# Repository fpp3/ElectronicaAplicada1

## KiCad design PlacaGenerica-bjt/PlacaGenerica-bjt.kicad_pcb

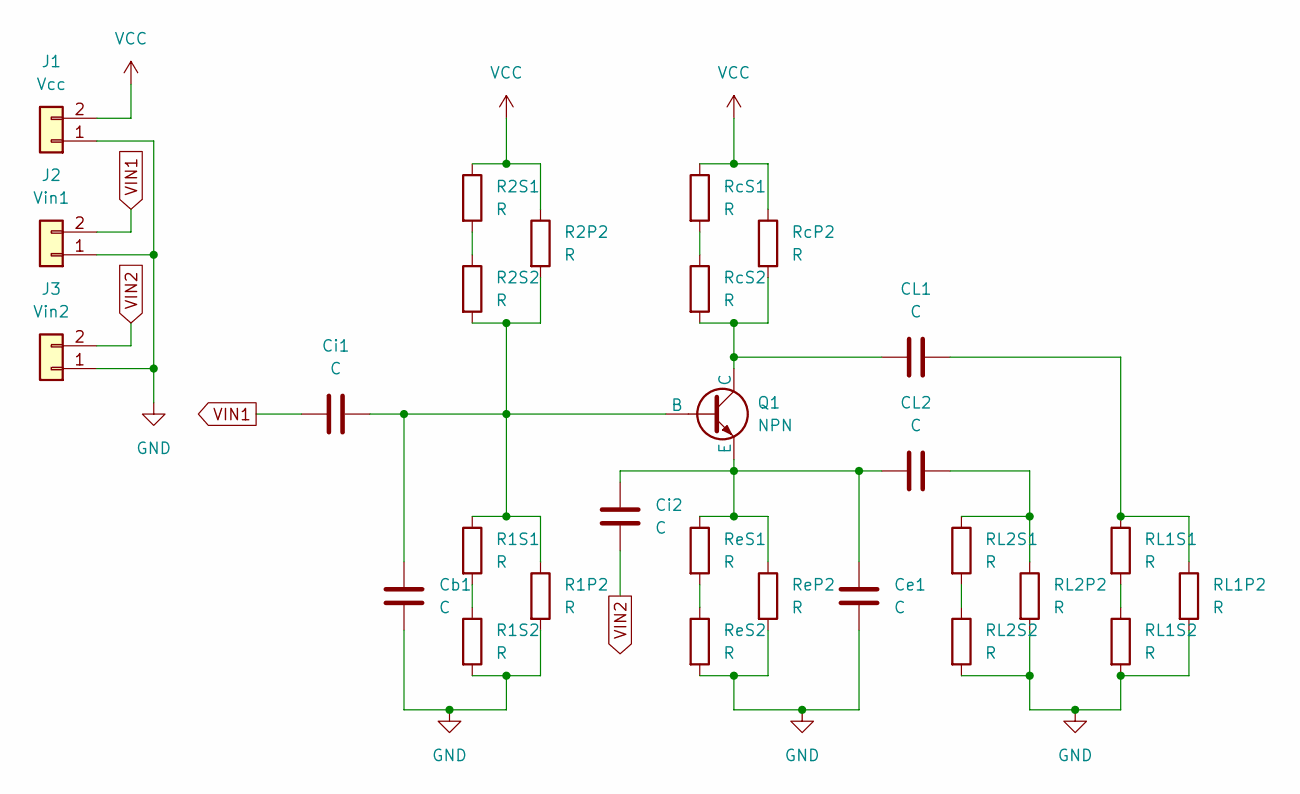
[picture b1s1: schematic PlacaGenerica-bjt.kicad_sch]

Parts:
CL1, CL2: C; Pretty-C_Disc_D5.0mm_W2.5mm_P5.00mm
Cb1: C; Pretty-C_Disc_D5.0mm_W2.5mm_P5.00mm
Ce1: C; Pretty-C_Disc_D5.0mm_W2.5mm_P5.00mm
Ci1, Ci2: C; Pretty-C_Disc_D5.0mm_W2.5mm_P5.00mm
J1: Vcc; TestPoint_2Pads_Pitch5.08mm_Drill1.3mm
J2: Vin1; TestPoint_2Pads_Pitch5.08mm_Drill1.3mm
J3: Vin2; TestPoint_2Pads_Pitch5.08mm_Drill1.3mm
Q1: NPN; Pretty-TO-92_Wide
R1P2, R1S1, R1S2, R2P2, R2S1, R2S2: R; Pretty-R_Axial_DIN0207_L6.3mm_D2.5mm_P7.62mm_Horizontal
RL1P2, RL1S1, RL1S2, RL2P2, RL2S1, RL2S2: R; Pretty-R_Axial_DIN0207_L6.3mm_D2.5mm_P7.62mm_Horizontal
RcP2: R; Pretty-R_Axial_DIN0207_L6.3mm_D2.5mm_P7.62mm_Horizontal
RcS1, RcS2: R; Pretty-R_Axial_DIN0207_L6.3mm_D2.5mm_P7.62mm_Horizontal
ReP2: R; Pretty-R_Axial_DIN0207_L6.3mm_D2.5mm_P7.62mm_Horizontal
ReS1, ReS2: R; Pretty-R_Axial_DIN0207_L6.3mm_D2.5mm_P7.62mm_Horizontal

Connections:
GND: Cb1.2, Ce1.2, J1.1, J2.1, J3.1, R1P2.2, R1S2.2, RL1P2.2, RL1S2.2, RL2P2.2, RL2S2.2, ReP2.2, ReS2.2
unnamed: CL1.2, RL1P2.1, RL1S1.1
unnamed: CL2.2, RL2P2.1, RL2S1.1
unnamed: Cb1.1, Ci1.2, Q1.2 (B), R1P2.1, R1S1.1, R2P2.2, R2S2.2
unnamed: CL1.1, Q1.1 (C), RcP2.2, RcS2.2
unnamed: CL2.1, Ce1.1, Ci2.1, Q1.3 (E), ReP2.1, ReS1.1
unnamed: R1S1.2, R1S2.1
unnamed: R2S1.2, R2S2.1
unnamed: RL1S1.2, RL1S2.1
unnamed: RL2S1.2, RL2S2.1
unnamed: RcS1.2, RcS2.1
unnamed: ReS1.2, ReS2.1
VCC: J1.2, R2P2.1, R2S1.1, RcP2.1, RcS1.1
VIN1: Ci1.1, J2.2
VIN2: Ci2.2, J3.2

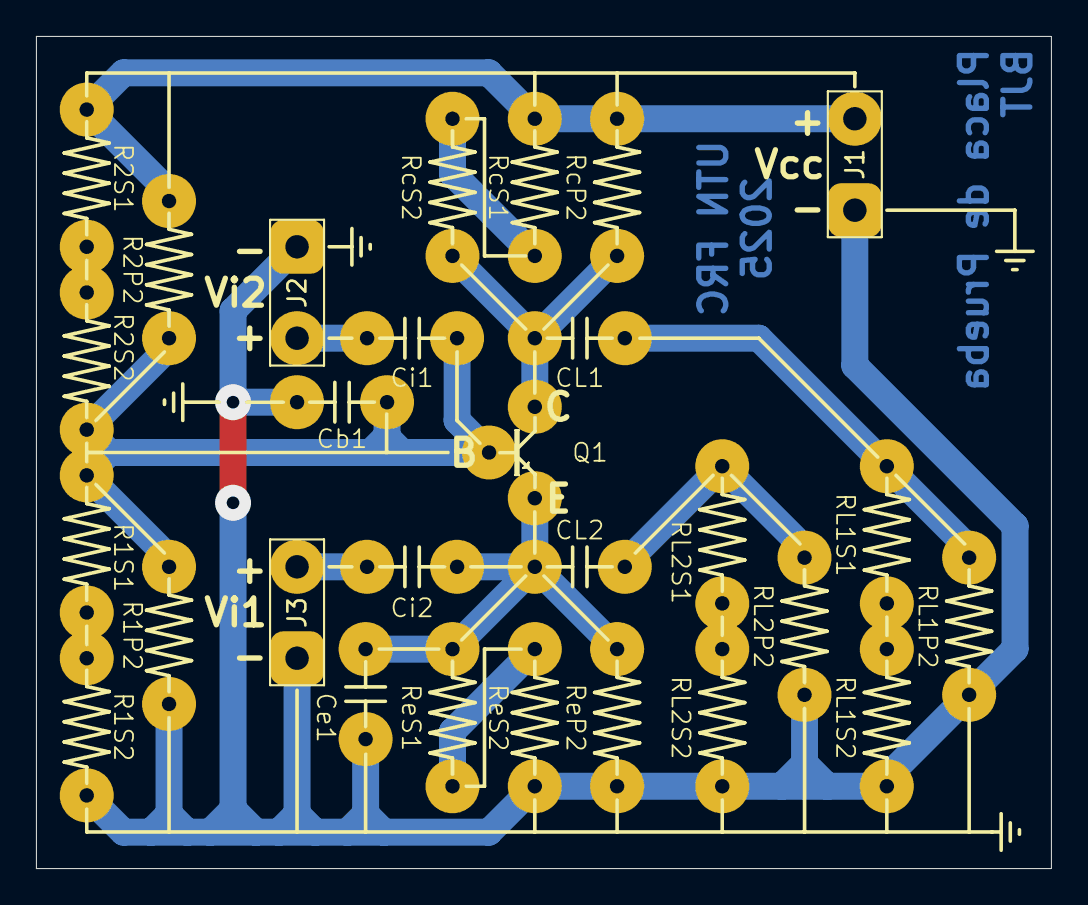
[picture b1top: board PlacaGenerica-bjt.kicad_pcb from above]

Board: 2 copper layers, 56.4 x 46.2 mm, 28 parts (0 on the bottom side), 15 nets.

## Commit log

2025-04-30 Add .gitignore for LaTeX
2025-04-30 tp1: Add base .tex
2025-04-30 tp1: introduccion
2025-05-08 tp1: Se añaden los capitulos necesarios
2025-05-15 cambios, no me acuerdo que
2025-05-18 seccion fuente no regulada terminada
2025-05-18 tp2: no era el tp1. Migra todo a "tp2/"
2025-05-18 tp2: Agrega mediciones de fuente regulada
2025-05-19 reestructuración fuente no regulada
2025-05-20 TP2: added conclusion and filtering and rectifying intro
2025-05-20 tp2: Ajustes de disposicion de figuras
2025-05-20 tp2: Termina de cocer lo que hizo gaston
2025-05-20 added regulator and others theoretical intro
2025-05-20 tp2: fotitos
2025-05-20 tp2: Agrega graficos en apartado de rectificacion
2025-05-20 tp2: Actualizacion de la introduccion al tp
2025-05-20 tp2: Correcciones y adiciones en apartado otros
2025-05-20 tp2: Correcciones menores
2025-05-20 tp2: Quita todos los trailing whitespaces
2025-05-20 tp2: Correccion de gramatica y ortografia
2025-05-21 tp2: Correccion seccion "filtrado"
2025-05-21 tp2: Agrega comparacion matematica del ripple
2025-05-21 tp2: Actualiza las conclusiones
2025-06-04 hola
2025-06-10 Actualiza PlacaGenerica-bjt para todos los lab
2025-06-13 Agrega serigrafia visual a PlacaGenerica-bjt
2025-08-13 TP3: creada carpeta y archivo tex
2025-08-13 Agrega Simulaciones
2025-08-16 Cambia circuito ampli porque estaba medio roto
2025-08-16 Sube json circuito amplificador
2025-08-16 Comienza seccion diseño para MES
2025-08-17 Comienza seccion calculo R1 y R2
2025-08-17 Completa capitulo 2
2025-08-17 Cambia a estructura por capitulos del doc
2025-08-17 Agrega archivos de diagramas
2025-08-17 Avanza piolamente en la seccion de MES
2025-08-17 Comienza seccion de simulacion
2025-08-18 Termina el capitulo 2
2025-08-18 Correcciones menores
2025-08-18 Agrega fotos osciloscopio
2025-08-18 TP3: añadidos 3 circuitos y casi finalizado cap 4
2025-08-18 TP4: creado el documento para hacer pp con latex
2025-08-19 TP3: terminado chapter 4?
2025-08-20 TP3: Conclusion y chachara
2025-08-20 Agrega introduccion
2025-08-20 Corrige recta de carga para resistencias precisas
2025-08-20 TP4: Agregadas simulaciones
2025-08-28 Restructura del proyecto
2025-08-31 TP4: Cambio de tema pp
2025-09-01 Avanza piolardo en sección de teoría
2025-09-01 tp4: agrega seccion de diseño, pto q y normaliz.
2025-09-01 tp4: agrega algunas labels
2025-09-01 tp4: termina seccion 2
2025-09-01 Creo que termina seccion teorica
2025-09-01 TP4: frame 4 y 5, y fotos
2025-09-02 tp4: correcciones menores
2025-09-03 TP4: corregido grafico y ecuacion cortadas
2025-09-03 TP4: agregado tema claro y corregido frame 4 vacio
2025-09-03 TP4: solucionada la section 4
2025-09-03 tp4: Retoques finales
2025-09-15 tp4: agrega devolucion
2025-10-29 tp5 iniciado
2025-10-30 cambios en la estructura del pdf
2025-10-30 Agrega algunos circuitos tp5
